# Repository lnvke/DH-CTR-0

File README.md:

# CTR-0
Cheaper Than aRduino is a custom devboard meant to be a cost-effective alternative my choice of the Arduino Nano series of devboard hobbyist microcontrollers. It is based of the same RP2040 microcontroller and will provide similar performance compared to its more costly counterpart, the Arduino Nano V3, which is the board I usually use for projects that require a microcontroller.

=======
## Roadmap
- finalize parts
  -finish footprints for any new parts
- pcb footprint, general size
  - placement/routing first pass
- cost optimization
- routing second pass
- final route optimization
- send gerbers to JLCPCB and order
- assemble
- done

## BOM links:

Capacitors:
0.1 uf https://www.digikey.com/en/products/detail/yageo/CC0402KRX7R7BB104/2103076
4.7 uf https://www.digikey.com/en/products/detail/yageo/CC0402MRX5R5BB475/5195139
10 uf https://www.digikey.com/en/products/detail/yageo/CC0603MRX5R5BB106/2833613
1 uf https://www.digikey.com/en/products/detail/yageo/CC0402KRX5R5BB105/2833744
15 pf https://www.digikey.com/en/products/detail/yageo/CC0402JRNPO9BN150/302751

Resistors:
5.1k https://www.digikey.com/en/products/detail/yageo/RC0402FR-075K1L/726624
27 https://www.digikey.com/en/products/detail/yageo/RC0402FR-0727RL/5280946
10k https://www.digikey.com/en/products/detail/yageo/RC0402FR-0710KL/726523
1k https://www.digikey.com/en/products/detail/yageo/RC0402FR-071KL/726513

Receptacles/Header Pins
THT 20h https://www.digikey.com/en/products/detail/sullins-connector-solutions/PRPC020SAAN-RC/2775234
THT 3h https://www.digikey.com/en/products/detail/sullins-connector-solutions/PRPC003SAAN-RC/2775251
USB4015 https://www.digikey.com/en/products/detail/gct/USB4105-GF-A/11198441

IC
TVS Diode https://www.digikey.com/en/products/detail/texas-instruments/TVS1400DRVR/8566097
NCP1117 https://www.digikey.com/en/products/detail/onsemi/NCP1117ST33T3G/1749063
Flash memory https://www.digikey.com/en/products/detail/macronix/MX25L12872FM2I-10G/10059507
RP2040 https://www.digikey.com/en/products/detail/raspberry-pi/SC0914-13/14306010
Crystal Resonator https://www.digikey.com/en/products/detail/abracon-llc/ABLS-12-000MHZ-B4-T/675654

Interface
SKRKAEE020 Push Button https://www.digikey.com/en/products/detail/alps-alpine/SKRKAEE020/19529176

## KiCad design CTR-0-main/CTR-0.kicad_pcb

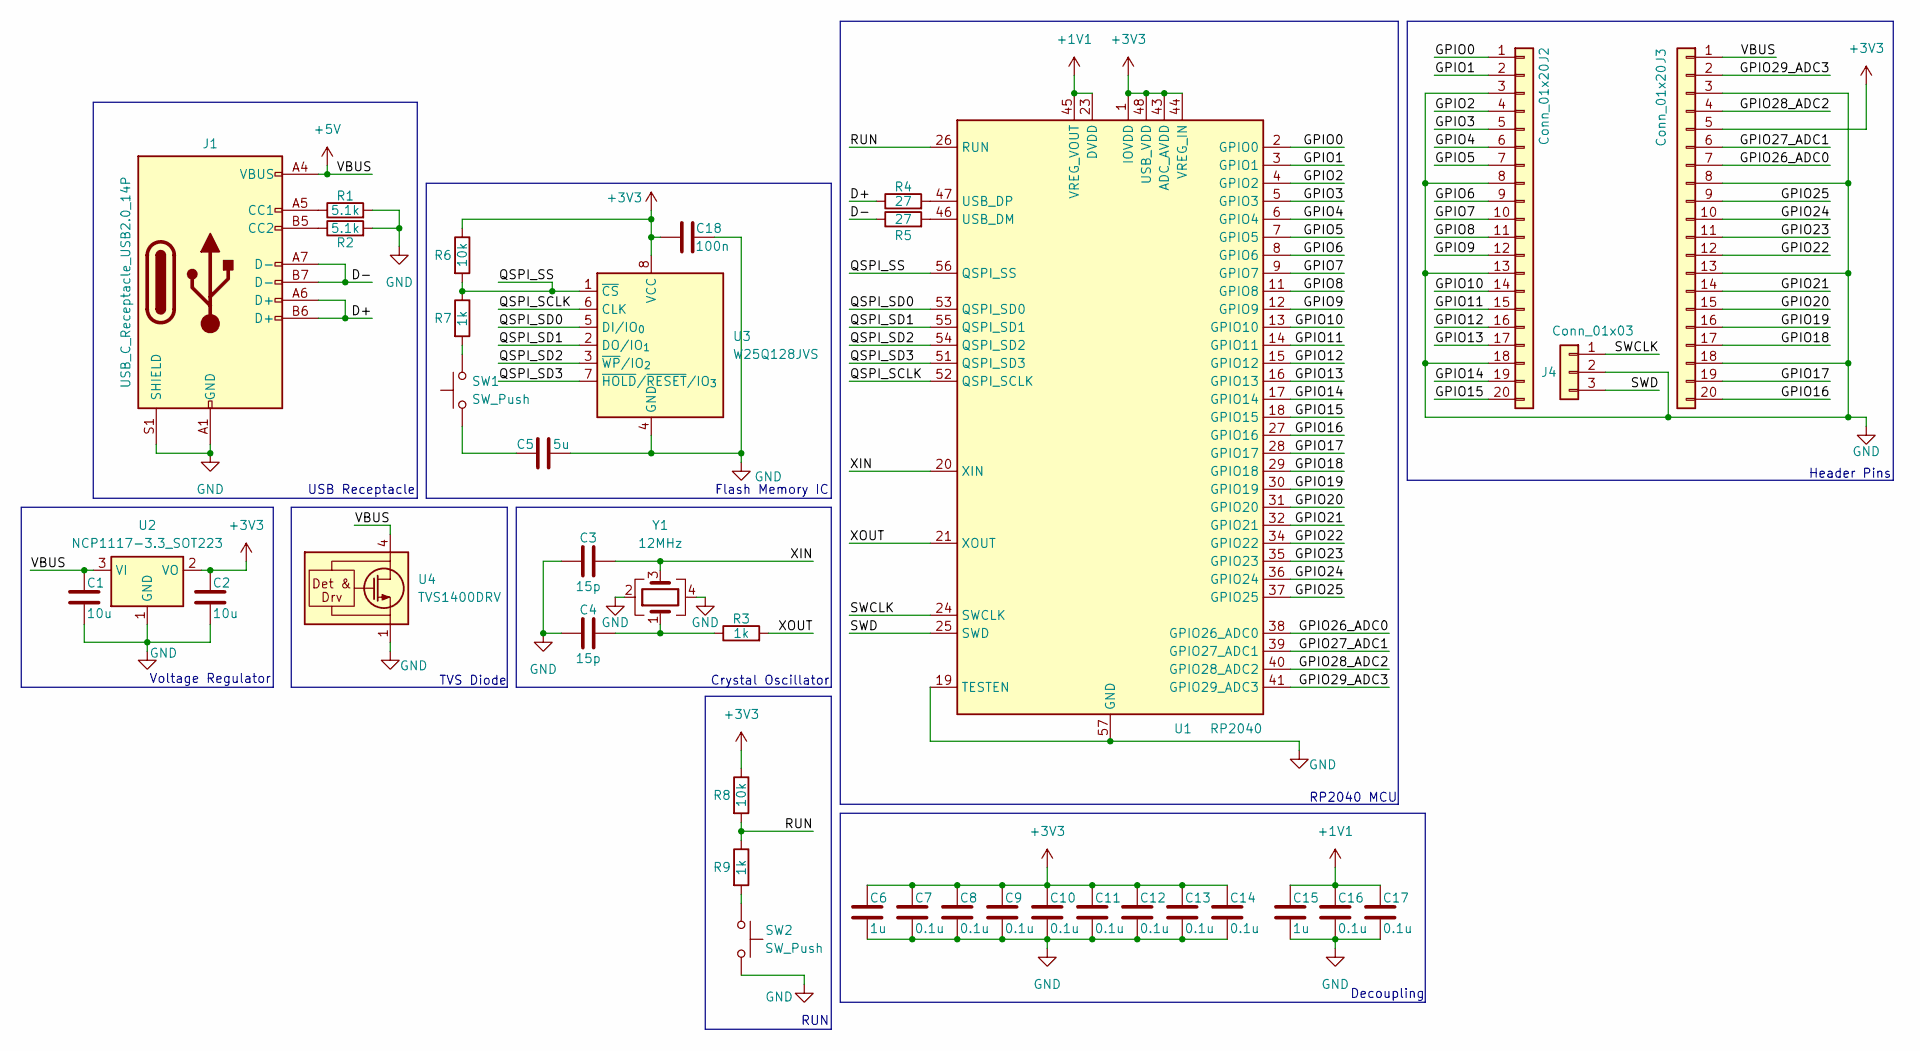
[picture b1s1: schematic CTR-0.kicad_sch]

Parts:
C1, C2: 10u; C_0603_1608Metric
C3, C4: 15p; C_0402_1005Metric
C5: 5u; C_0402_1005Metric
C6, C15: 1u; C_0402_1005Metric
C7, C8, C9, C10, C11, C12, C13, C14, C16, C17: 0.1u; C_0402_1005Metric
C18: 100n; C_0402_1005Metric
J1: USB_C_Receptacle_USB2.0_14P; USB_C_Receptacle_HRO_TYPE-C-31-M-12
J2, J3: Conn_01x20; PinHeader_1x20_P2.54mm_Vertical
J4: Conn_01x03; PinHeader_1x03_P2.54mm_Vertical
R1, R2: 5.1k; R_0402_1005Metric
R3, R7, R9: 1k; R_0402_1005Metric
R4, R5: 27; R_0402_1005Metric
R6, R8: 10k; R_0402_1005Metric
SW1, SW2: SW_Push; SW_Push_SPST_NO_Alps_SKRK
U1: RP2040; QFN-56-1EP_7x7mm_P0.4mm_EP3.2x3.2mm
U2: NCP1117-3.3_SOT223; SOT-223-3_TabPin2
U3: W25Q128JVS; SOIC-8_5.3x5.3mm_P1.27mm
U4: TVS1400DRV; WSON-6-1EP_2x2mm_P0.65mm_EP1x1.6mm
Y1: 12MHz; Crystal_SMD_3225-4Pin_3.2x2.5mm

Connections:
+1V1: C15.1, C16.1, C17.1, U1.23 (DVDD), U1.45 (VREG_VOUT), U1.50 (DVDD)
+3V3: C2.1, C6.1, C7.1, C8.1, C9.1, C10.1, C11.1, C12.1, C13.1, C14.1, C18.2, J3.5, R6.1, R8.1, U1.1 (IOVDD), U1.10 (IOVDD), U1.22 (IOVDD), U1.33 (IOVDD), U1.42 (IOVDD), U1.43 (ADC_AVDD), U1.44 (VREG_IN), U1.48 (USB_VDD), U1.49 (IOVDD), U2.2 (VO), U3.8 (VCC)
+5V: C1.1, J1.A4 (VBUS), J1.A9 (VBUS), J1.B4 (VBUS), J1.B9 (VBUS), J3.1, U2.3 (VI), U4.4 (IN), U4.5 (IN), U4.6 (IN)
/D+: J1.A6 (D+), J1.B6 (D+), R4.1
/D-: J1.A7 (D-), J1.B7 (D-), R5.1
/GPIO0: J2.1, U1.2 (GPIO0)
/GPIO1: J2.2, U1.3 (GPIO1)
/GPIO2: J2.4, U1.4 (GPIO2)
/GPIO3: J2.5, U1.5 (GPIO3)
/GPIO4: J2.6, U1.6 (GPIO4)
/GPIO5: J2.7, U1.7 (GPIO5)
/GPIO6: J2.9, U1.8 (GPIO6)
/GPIO7: J2.10, U1.9 (GPIO7)
/GPIO8: J2.11, U1.11 (GPIO8)
/GPIO9: J2.12, U1.12 (GPIO9)
/GPIO10: J2.14, U1.13 (GPIO10)
/GPIO11: J2.15, U1.14 (GPIO11)
/GPIO12: J2.16, U1.15 (GPIO12)
/GPIO13: J2.17, U1.16 (GPIO13)
/GPIO14: J2.19, U1.17 (GPIO14)
/GPIO15: J2.20, U1.18 (GPIO15)
/GPIO16: J3.20, U1.27 (GPIO16)
/GPIO17: J3.19, U1.28 (GPIO17)
/GPIO18: J3.17, U1.29 (GPIO18)
/GPIO19: J3.16, U1.30 (GPIO19)
/GPIO20: J3.15, U1.31 (GPIO20)
/GPIO21: J3.14, U1.32 (GPIO21)
/GPIO22: J3.12, U1.34 (GPIO22)
/GPIO23: J3.11, U1.35 (GPIO23)
/GPIO24: J3.10, U1.36 (GPIO24)
/GPIO25: J3.9, U1.37 (GPIO25)
/GPIO26_ADC0: J3.7, U1.38 (GPIO26_ADC0)
/GPIO27_ADC1: J3.6, U1.39 (GPIO27_ADC1)
/GPIO28_ADC2: J3.4, U1.40 (GPIO28_ADC2)
/GPIO29_ADC3: J3.2, U1.41 (GPIO29_ADC3)
/QSPI_SCLK: U1.52 (QSPI_SCLK), U3.6 (CLK)
/QSPI_SD0: U1.53 (QSPI_SD0), U3.5 (DI/IO_{0})
/QSPI_SD1: U1.55 (QSPI_SD1), U3.2 (DO/IO_{1})
/QSPI_SD2: U1.54 (QSPI_SD2), U3.3 (~WP/IO_{2})
/QSPI_SD3: U1.51 (QSPI_SD3), U3.7 (~HOLD/~RESET/IO_{3})
/QSPI_SS: R6.2, R7.1, U1.56 (QSPI_SS), U3.1 (~CS)
/RUN: R8.2, R9.1, U1.26 (RUN)
/SWCLK: J4.1, U1.24 (SWCLK)
/SWD: J4.3, U1.25 (SWD)
/XIN: C3.2, U1.20 (XIN), Y1.3
/XOUT: R3.2, U1.21 (XOUT)
GND: C1.2, C2.2, C3.1, C4.1, C5.1, C6.2, C7.2, C8.2, C9.2, C10.2, C11.2, C12.2, C13.2, C14.2, C15.2, C16.2, C17.2, C18.1, J1.A1 (GND), J1.A12 (GND), J1.B1 (GND), J1.B12 (GND), J1.S1 (SHIELD), J2.3, J2.8, J2.13, J2.18, J3.3, J3.8, J3.13, J3.18, J4.2, R1.2, R2.2, SW2.1, U1.19 (TESTEN), U1.57 (GND), U2.1 (GND), U3.4 (GND), U4.1 (GND), U4.2 (GND), U4.3 (GND), U4.7 (GND), Y1.2, Y1.4
unnamed: C4.2, R3.1, Y1.1
unnamed: C5.2, SW1.1
unnamed: J1.A5 (CC1), R1.1
unnamed: J1.B5 (CC2), R2.1
unnamed: R7.2, SW1.2
unnamed: R9.2, SW2.2
unnamed: R5.2, U1.46 (USB_DM)
unnamed: R4.2, U1.47 (USB_DP)

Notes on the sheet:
RP2040 MCU
Flash Memory IC
Crystal Oscillator
Decoupling
RUN
TVS Diode
Voltage Regulator
USB Receptacle
Header Pins

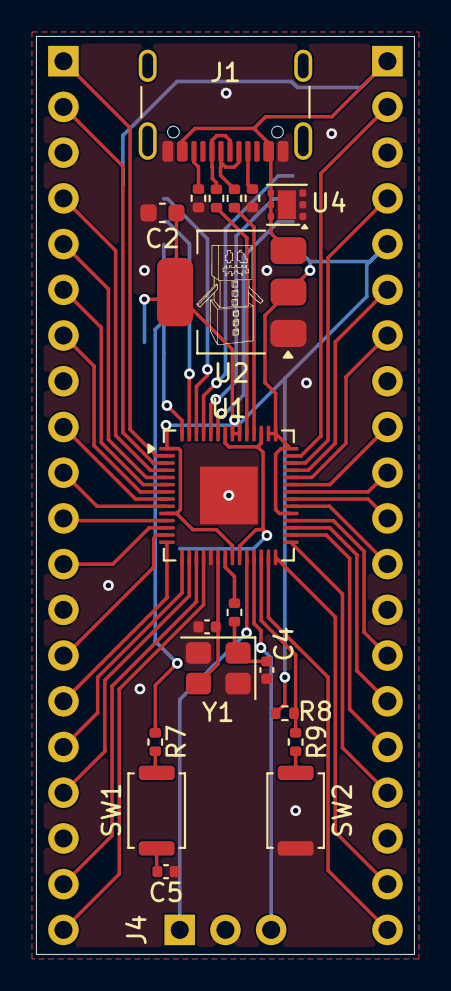
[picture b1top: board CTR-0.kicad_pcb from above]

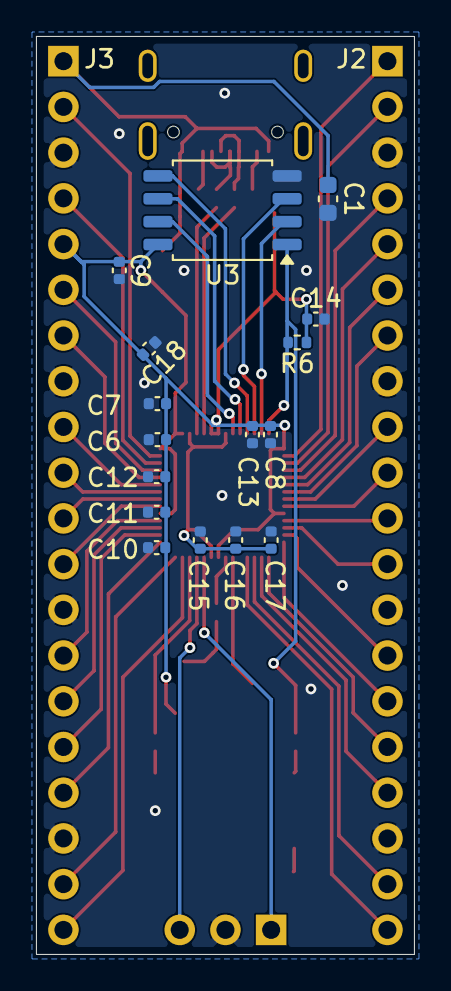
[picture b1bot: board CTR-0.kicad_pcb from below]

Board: 2 copper layers, 21.0 x 51.0 mm, 38 parts (18 on the bottom side), 55 nets.

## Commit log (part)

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2026-03-23 uploaded .pro file for further work
2026-03-28 fixed lost data
    remade schematic, re-applied footprints, and rerouted first pass of pcb
2026-04-02 Delete CTR-0 directory
    false directory
2026-04-09 3rd pass
    repositioned, made full use of board, optimized routing
2026-04-19 Add files via upload
    fixed drc gnd net
2026-04-23 fix
    minor fixes to last push
2026-04-23 removed excess files
2026-04-24 organization
    changed file location for bom
2026-04-24 add
    gerber
2026-04-24 update
    fixed gerbers
2026-04-25 fix
    silkscreen
2026-04-27 edit
    i lowkey dont know what
2026-05-02 edit
    readme links done
